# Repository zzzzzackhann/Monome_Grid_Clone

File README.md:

FOR NEXT TIME:

1. Find an LED driver than operates the same way your logic decoder works for easier wiring

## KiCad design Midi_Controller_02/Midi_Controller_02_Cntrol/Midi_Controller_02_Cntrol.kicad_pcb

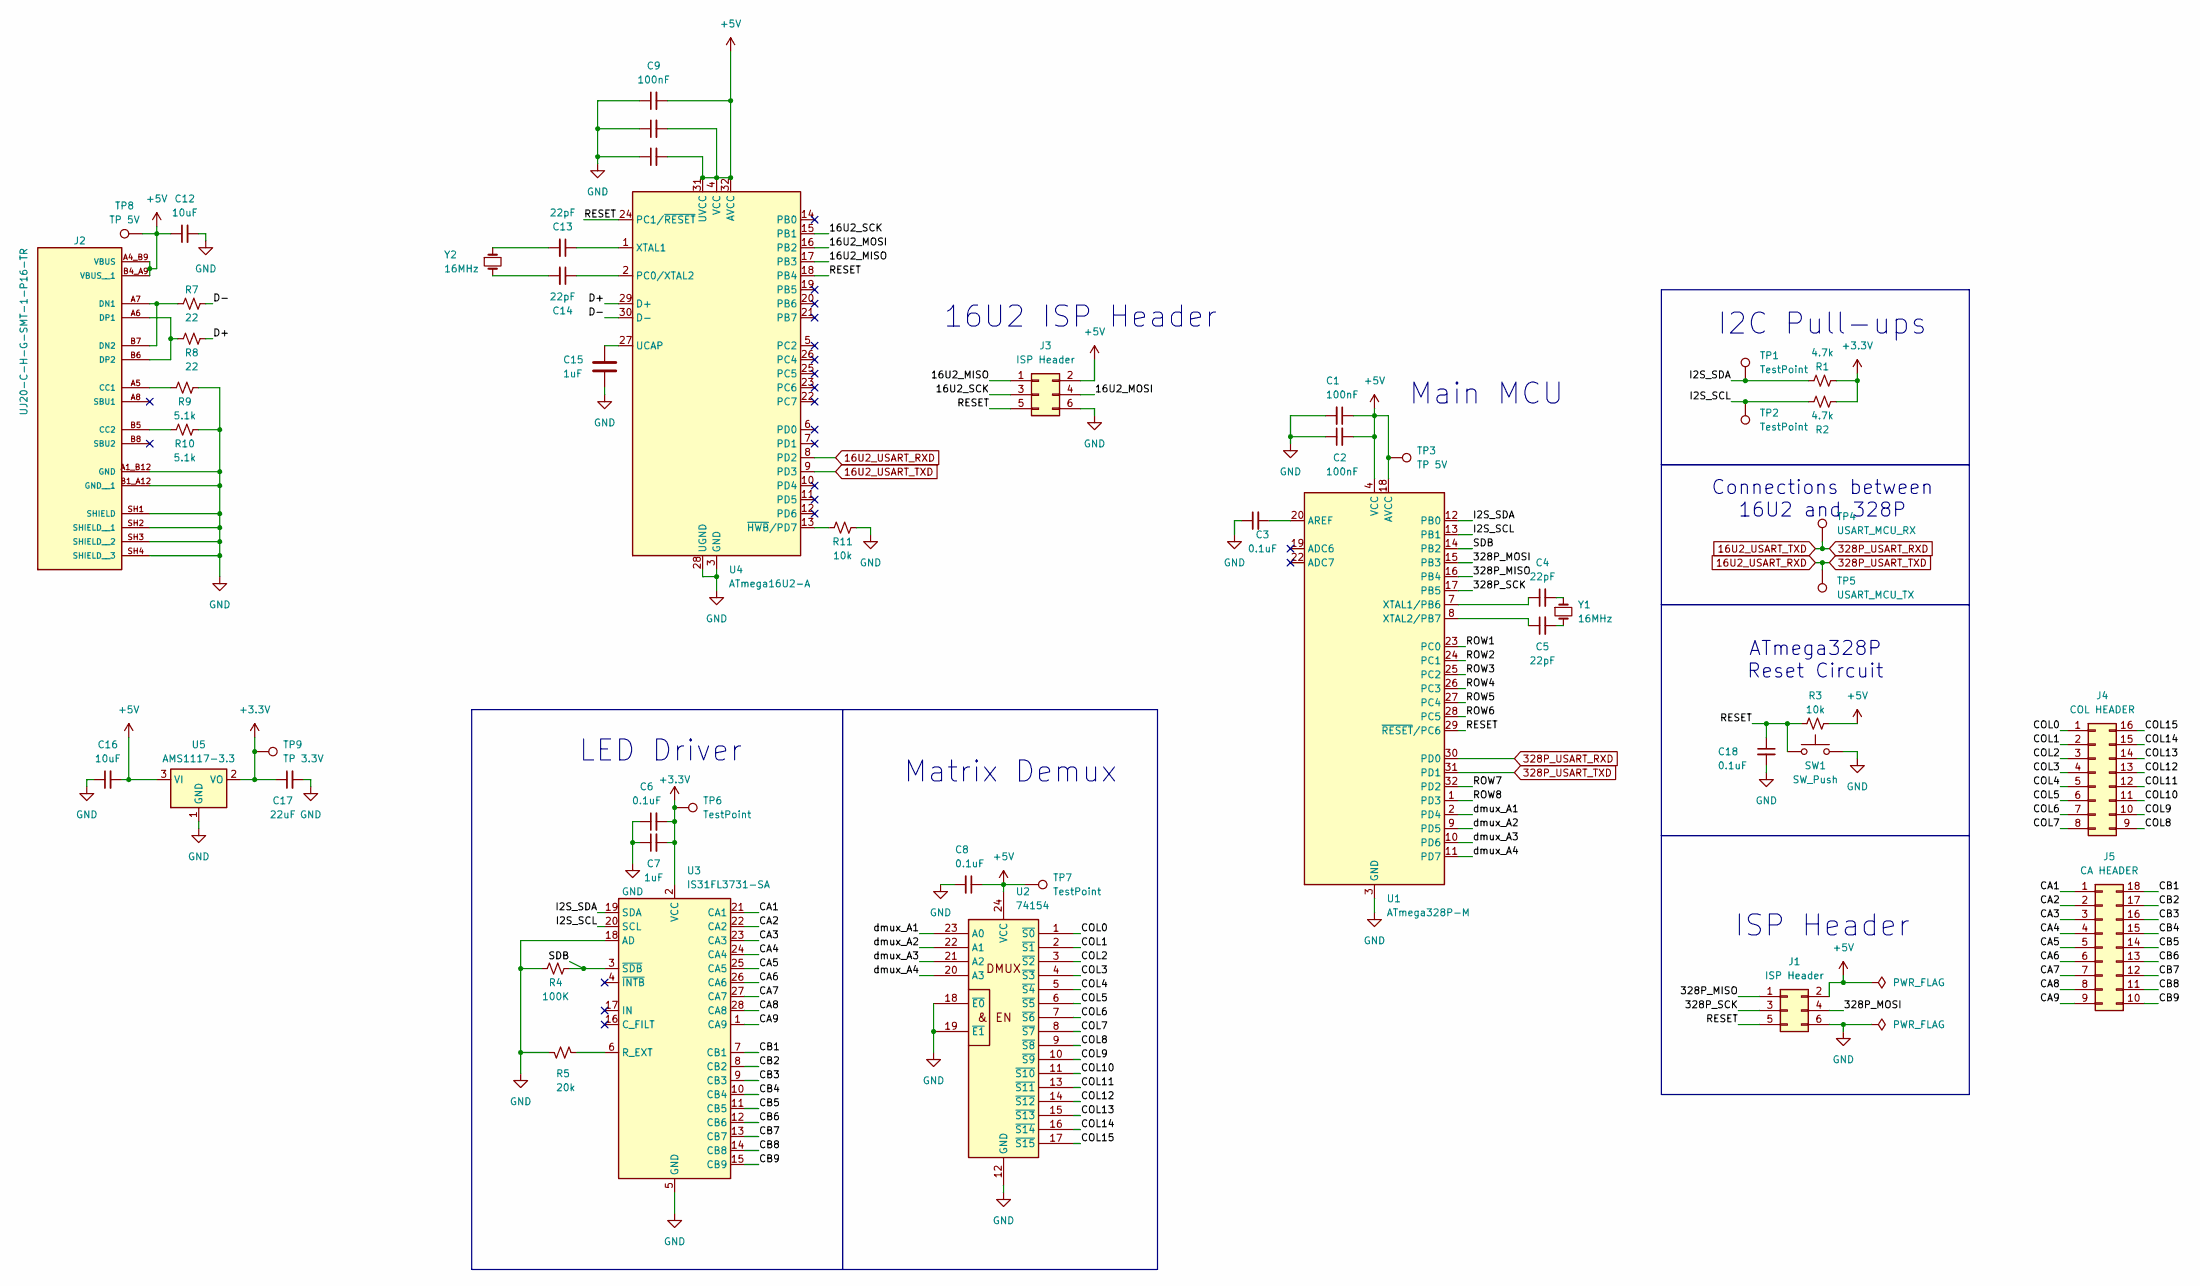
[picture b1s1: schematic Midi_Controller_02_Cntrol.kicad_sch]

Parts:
C1, C2, C9, C10, C11: 100nF; C_0805_2012Metric
C3, C6, C8, C18: 0.1uF; C_0805_2012Metric
C4, C5, C13, C14: 22pF; C_0805_2012Metric
C7, C15: 1uF; C_0805_2012Metric
C12, C16: 10uF; C_0805_2012Metric
C17: 22uF; C_0805_2012Metric
J1, J3: ISP Header; TestPoint_Pad_D1.0mm_2x3
J2: UJ20-C-H-G-SMT-1-P16-TR; SAMESKY_UJ20-C-H-G-SMT-1-P16-TR; PARTREV 1.0
J4: COL HEADER; PinHeader_2x08_P2.54mm_Horizontal
J5: CA HEADER; PinHeader_2x09_P2.54mm_Horizontal
R1, R2: 4.7k; R_0805_2012Metric
R3, R11: 10k; R_0805_2012Metric
R4: 100K; R_0805_2012Metric
R5: 20k; R_0805_2012Metric
R7, R8: 22; R_0805_2012Metric
R9, R10: 5.1k; R_0805_2012Metric
SW1: SW_Push; SW_TS04-66-55-BK-100-SMT
TP1, TP2: TestPoint; SolderWire-0.5sqmm_1x01_D0.9mm_OD2.3mm
TP3, TP8: TP 5V; TestPoint_Pad_D1.5mm
TP4: USART_MCU_RX; SolderWire-0.5sqmm_1x01_D0.9mm_OD2.3mm
TP5: USART_MCU_TX; SolderWire-0.5sqmm_1x01_D0.9mm_OD2.3mm
TP6, TP7: TestPoint; TestPoint_Pad_D1.5mm
TP9: TP 3.3V; TestPoint_Pad_D1.5mm
U1: ATmega328P-M; QFN-32-1EP_5x5mm_P0.5mm_EP3.1x3.1mm
U2: 74154; SOIC-24W_7.5x15.4mm_P1.27mm
U3: IS31FL3731-SA; SSOP-28_5.3x10.2mm_P0.65mm
U4: ATmega16U2-A; TQFP-32_7x7mm_P0.8mm
U5: AMS1117-3.3; SOT-223-3_TabPin2
Y1, Y2: 16MHz; Crystal_HC49-4H_Vertical

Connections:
16U2_USART_RXD: TP5.1 (1_1), U1.31 (PD1), U4.8 (PD2)
16U2_USART_TXD: TP4.1 (1_1), U1.30 (PD0), U4.9 (PD3)
+3.3V: C6.2, C7.2, C17.1, R1.1, R2.1, TP6.1 (1_1), TP9.1 (1_1), U3.2 (VCC), U5.2 (VO)
+5V: C1.1, C2.2, C8.1, C9.2, C10.2, C11.2, C12.1, C16.2, J1.2, J2.A4_B9 (VBUS), J2.B4_A9 (VBUS__1), J3.2, R3.2, TP3.1 (1_1), TP7.1 (1_1), TP8.1 (1_1), U1.4 (VCC), U1.6 (VCC), U1.18 (AVCC), U2.24 (VCC), U4.4 (VCC), U4.31 (UVCC), U4.32 (AVCC), U5.3 (VI)
/16U2_MISO: J3.1, U4.17 (PB3)
/16U2_MOSI: J3.4, U4.16 (PB2)
/16U2_SCK: J3.3, U4.15 (PB1)
/328P_MISO: J1.1, U1.16 (PB4)
/328P_MOSI: J1.4, U1.15 (PB3)
/328P_SCK: J1.3, U1.17 (PB5)
/CA1: J5.1, U3.21 (CA1)
/CA2: J5.2, U3.22 (CA2)
/CA3: J5.3, U3.23 (CA3)
/CA4: J5.4, U3.24 (CA4)
/CA5: J5.5, U3.25 (CA5)
/CA6: J5.6, U3.26 (CA6)
/CA7: J5.7, U3.27 (CA7)
/CA8: J5.8, U3.28 (CA8)
/CA9: J5.9, U3.1 (CA9)
/CB1: J5.18, U3.7 (CB1)
/CB2: J5.17, U3.8 (CB2)
/CB3: J5.16, U3.9 (CB3)
/CB4: J5.15, U3.10 (CB4)
/CB5: J5.14, U3.11 (CB5)
/CB6: J5.13, U3.12 (CB6)
/CB7: J5.12, U3.13 (CB7)
/CB8: J5.11, U3.14 (CB8)
/CB9: J5.10, U3.15 (CB9)
/COL0: J4.1, U2.1 (~S0)
/COL1: J4.2, U2.2 (~S1)
/COL2: J4.3, U2.3 (~S2)
/COL3: J4.4, U2.4 (~S3)
/COL4: J4.5, U2.5 (~S4)
/COL5: J4.6, U2.6 (~S5)
/COL6: J4.7, U2.7 (~S6)
/COL7: J4.8, U2.8 (~S7)
/COL8: J4.9, U2.9 (~S8)
/COL9: J4.10, U2.10 (~S9)
/COL10: J4.11, U2.11 (~S10)
/COL11: J4.12, U2.13 (~S11)
/COL12: J4.13, U2.14 (~S12)
/COL13: J4.14, U2.15 (~S13)
/COL14: J4.15, U2.16 (~S14)
/COL15: J4.16, U2.17 (~S15)
/D+: R8.1, U4.29 (D+)
/D-: R7.2, U4.30 (D-)
/I2S_SCL: R2.2, TP2.1 (1_1), U1.13 (PB1), U3.20 (SCL)
/I2S_SDA: R1.2, TP1.1 (1_1), U1.12 (PB0), U3.19 (SDA)
/RESET: C18.1, J1.5, J3.5, R3.1, SW1.1, U1.29 (~RESET/PC6), U4.18 (PB4), U4.24 (PC1/~RESET)
/ROW1: U1.23 (PC0)
/ROW2: U1.24 (PC1)
/ROW3: U1.25 (PC2)
/ROW4: U1.26 (PC3)
/ROW5: U1.27 (PC4)
/ROW6: U1.28 (PC5)
/ROW7: U1.32 (PD2)
/ROW8: U1.1 (PD3)
/SDB: R4.2, U1.14 (PB2), U3.3 (~SDB)
/dmux_A1: U1.2 (PD4), U2.23 (A0)
/dmux_A2: U1.9 (PD5), U2.22 (A1)
/dmux_A3: U1.10 (PD6), U2.21 (A2)
/dmux_A4: U1.11 (PD7), U2.20 (A3)
GND: C1.2, C2.1, C3.1, C6.1, C7.1, C8.2, C9.1, C10.1, C11.1, C12.2, C15.2, C16.1, C17.2, C18.2, J1.6, J2.A1_B12 (GND), J2.B1_A12 (GND__1), J2.SH1 (SHIELD), J2.SH2 (SHIELD__1), J2.SH3 (SHIELD__2), J2.SH4 (SHIELD__3), J3.6, R4.1, R5.1, R9.2, R10.1, R11.1, SW1.2, U1.3 (GND), U1.5 (GND), U1.21 (GND), U1.33 (GND), U2.12 (GND), U2.18 (~E0), U2.19 (~E1), U3.5 (GND), U3.18 (AD), U4.3 (GND), U4.28 (UGND), U5.1 (GND)
unnamed: C4.2, Y1.1
unnamed: C5.2, Y1.2
unnamed: C13.2, Y2.1
unnamed: C14.2, Y2.2
unnamed: J2.A5 (CC1), R9.1
unnamed: J2.B5 (CC2), R10.2
unnamed: J2.A7 (DN1), J2.B7 (DN2), R7.1
unnamed: J2.A6 (DP1), J2.B6 (DP2), R8.2
unnamed: C3.2, U1.20 (AREF)
unnamed: C4.1, U1.7 (XTAL1/PB6)
unnamed: C5.1, U1.8 (XTAL2/PB7)
unnamed: R5.2, U3.6 (R_EXT)
unnamed: C14.1, U4.2 (PC0/XTAL2)
unnamed: C15.1, U4.27 (UCAP)
unnamed: C13.1, U4.1 (XTAL1)
unnamed: R11.2, U4.13 (~HWB/PD7)

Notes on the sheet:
Main MCU
LED Driver
ISP Header
I2C Pull-ups
Connections between 16U2 and 328P
ATmega328P Reset Circuit
16U2 ISP Header
Matrix Demux

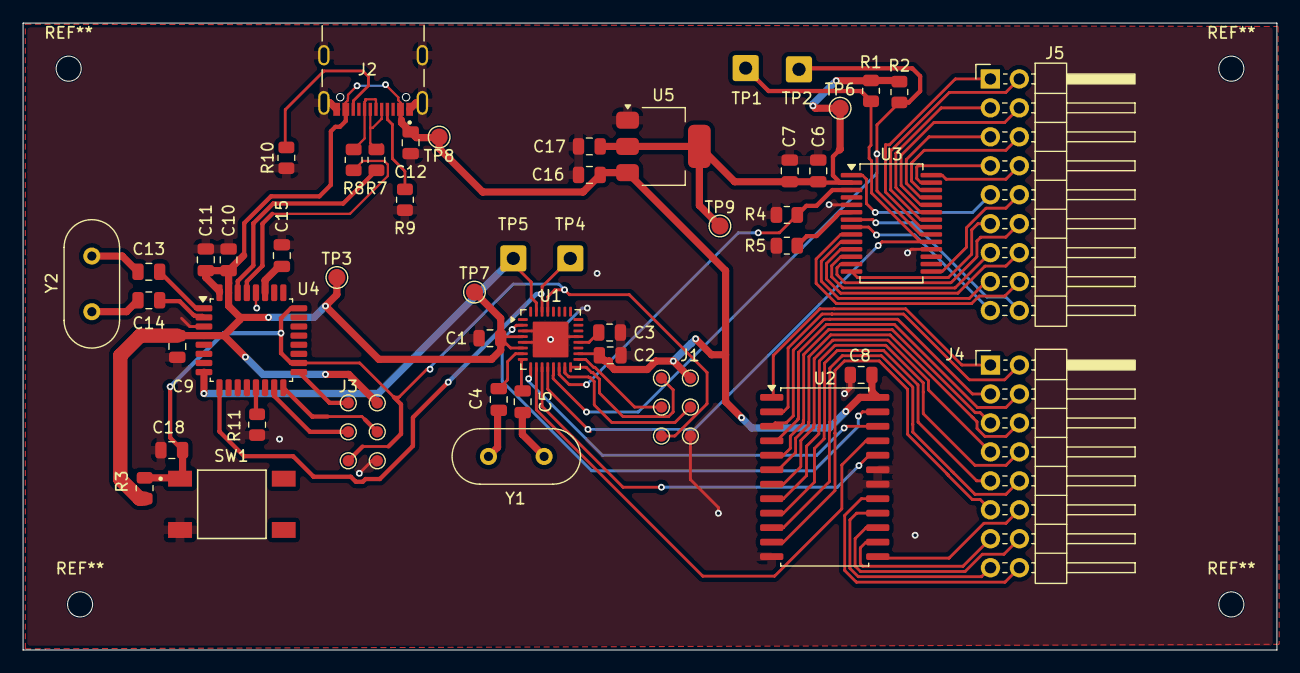
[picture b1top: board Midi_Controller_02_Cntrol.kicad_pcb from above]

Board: 2 copper layers, 110.0 x 55.0 mm, 50 parts (0 on the bottom side), 71 nets.

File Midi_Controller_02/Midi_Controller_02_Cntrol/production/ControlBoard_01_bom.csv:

Designator,Footprint,Quantity,Value,LCSC Part #
"C1, C10, C11, C2, C9",0805,5,100nF,
"C12, C16",0805,2,10uF,
"C13, C14, C4, C5",0805,4,22pF,
"C15, C7",0805,2,1uF,
C17,0805,1,20uF,
"C18, C3, C6, C8",0805,4,0.1uF,
"J1, J3",TestPoint_Pad_D1.0mm_2x3,2,ISP Header,
J2,SAMESKY_UJ20-C-H-G-SMT-1-P16-TR,1,UJ20-C-H-G-SMT-1-P16-TR,
J4,PinHeader_2x08_P2.54mm_Horizontal,1,COL HEADER,
J5,PinHeader_2x09_P2.54mm_Horizontal,1,CA HEADER,
"R1, R2",0805,2,4.7k,
"R10, R9",0805,2,5.1k,
"R11, R3",0805,2,10k,
R4,0805,1,100K,
R5,0805,1,20k,
"R7, R8",0805,2,22,
SW1,SW_TS04-66-55-BK-100-SMT,1,SW_Push,
"TP1, TP2",SolderWire-0.5sqmm_1x01_D0.9mm_OD2.3mm,2,TestPoint,
"TP3, TP8",TestPoint_Pad_D1.5mm,2,TP 5V,
TP4,SolderWire-0.5sqmm_1x01_D0.9mm_OD2.3mm,1,USART_MCU_RX,
TP5,SolderWire-0.5sqmm_1x01_D0.9mm_OD2.3mm,1,USART_MCU_TX,
"TP6, TP7",TestPoint_Pad_D1.5mm,2,TestPoint,
TP9,TestPoint_Pad_D1.5mm,1,TP 3.3V,
U1,QFN-32-1EP_5x5mm_P0.5mm_EP3.1x3.1mm,1,ATmega328P-M,
U2,SOIC-24W_7.5x15.4mm_P1.27mm,1,74154,
U3,SSOP-28_5.3x10.2mm_P0.65mm,1,IS31FL3731-SA,
U4,TQFP-32_7x7mm_P0.8mm,1,ATmega16U2-A,
U5,SOT-223-3_TabPin2,1,AMS1117-3.3,
"Y1, Y2",Crystal_HC49-4H_Vertical,2,16MHz,

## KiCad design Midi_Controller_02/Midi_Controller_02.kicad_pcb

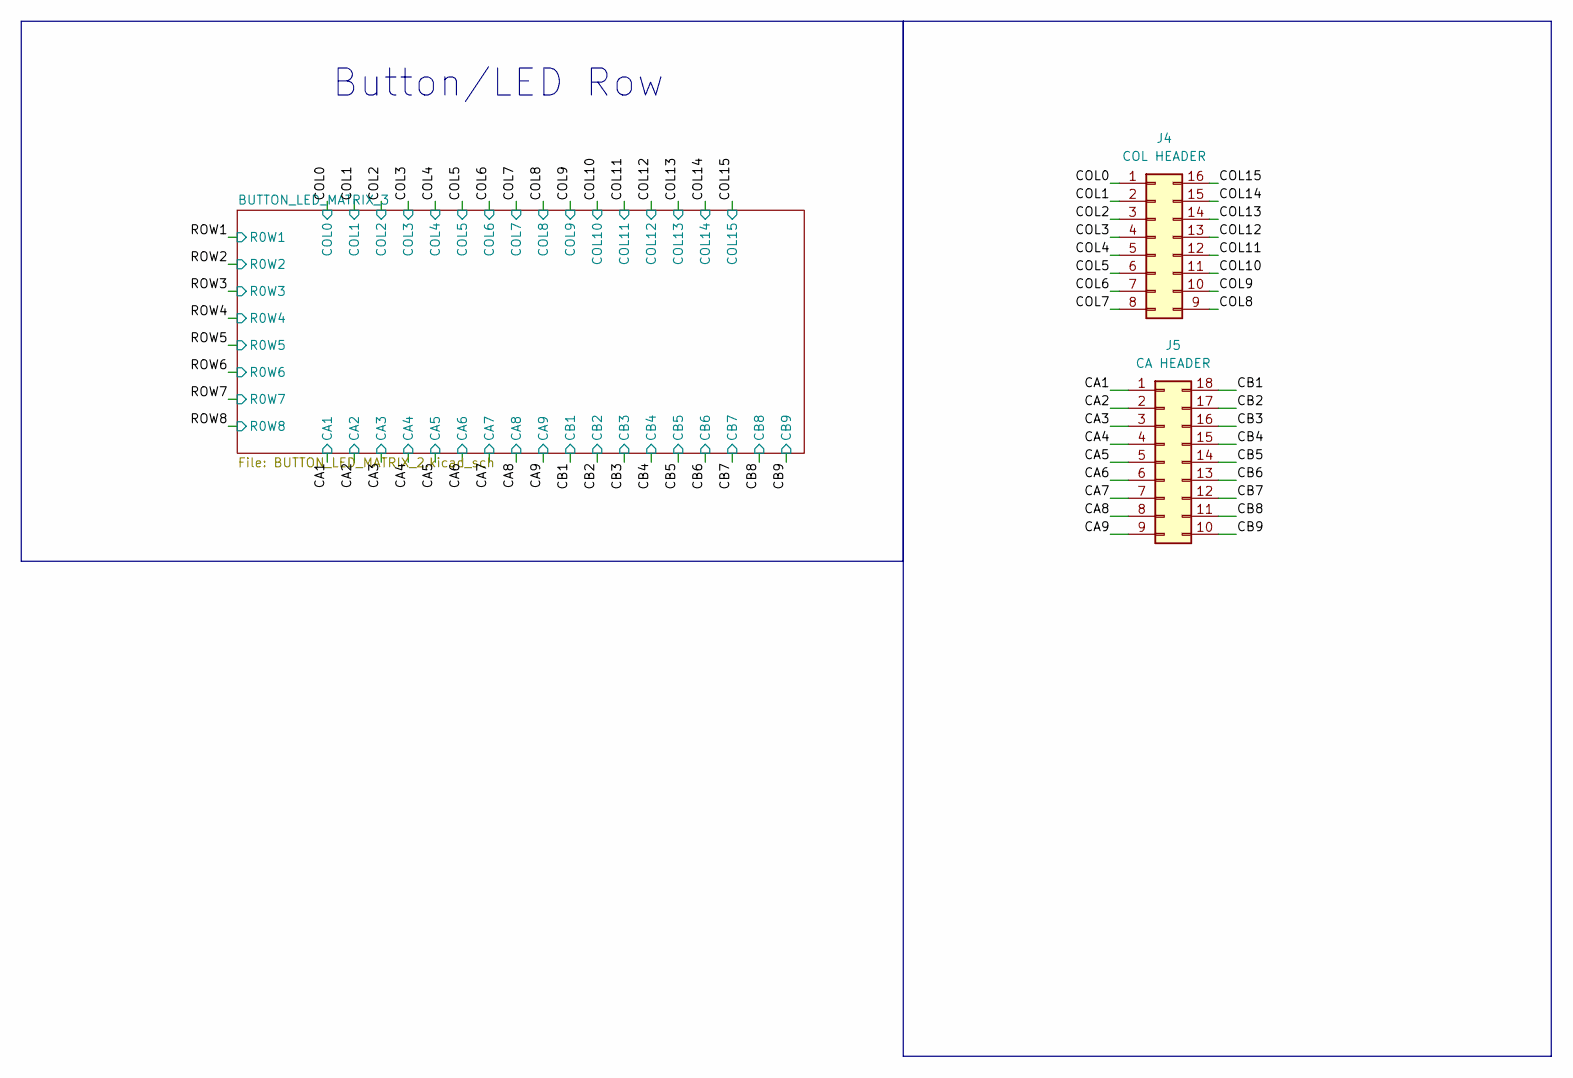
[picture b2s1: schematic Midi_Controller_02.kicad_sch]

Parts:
J4: COL HEADER; PinHeader_2x08_P2.54mm_Vertical
J5: CA HEADER; PinHeader_2x09_P2.54mm_Vertical

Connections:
/CONTROLLER-MATRIX/CA1: J5.1; also elsewhere on the board
/CONTROLLER-MATRIX/CA2: J5.2; also elsewhere on the board
/CONTROLLER-MATRIX/CA3: J5.3; also elsewhere on the board
/CONTROLLER-MATRIX/CA4: J5.4; also elsewhere on the board
/CONTROLLER-MATRIX/CA5: J5.5; also elsewhere on the board
/CONTROLLER-MATRIX/CA6: J5.6; also elsewhere on the board
/CONTROLLER-MATRIX/CA7: J5.7; also elsewhere on the board
/CONTROLLER-MATRIX/CA8: J5.8; also elsewhere on the board
/CONTROLLER-MATRIX/CA9: J5.9; also elsewhere on the board
/CONTROLLER-MATRIX/CB1: J5.18; also elsewhere on the board
/CONTROLLER-MATRIX/CB2: J5.17; also elsewhere on the board
/CONTROLLER-MATRIX/CB3: J5.16; also elsewhere on the board
/CONTROLLER-MATRIX/CB4: J5.15; also elsewhere on the board
/CONTROLLER-MATRIX/CB5: J5.14; also elsewhere on the board
/CONTROLLER-MATRIX/CB6: J5.13; also elsewhere on the board
/CONTROLLER-MATRIX/CB7: J5.12; also elsewhere on the board
/CONTROLLER-MATRIX/CB8: J5.11; also elsewhere on the board
/CONTROLLER-MATRIX/CB9: J5.10; also elsewhere on the board
/CONTROLLER-MATRIX/COL0: J4.1; also elsewhere on the board
/CONTROLLER-MATRIX/COL1: J4.2; also elsewhere on the board
/CONTROLLER-MATRIX/COL2: J4.3; also elsewhere on the board
/CONTROLLER-MATRIX/COL3: J4.4; also elsewhere on the board
/CONTROLLER-MATRIX/COL4: J4.5; also elsewhere on the board
/CONTROLLER-MATRIX/COL5: J4.6; also elsewhere on the board
/CONTROLLER-MATRIX/COL6: J4.7; also elsewhere on the board
/CONTROLLER-MATRIX/COL7: J4.8; also elsewhere on the board
/CONTROLLER-MATRIX/COL8: J4.9; also elsewhere on the board
/CONTROLLER-MATRIX/COL9: J4.10; also elsewhere on the board
/CONTROLLER-MATRIX/COL10: J4.11; also elsewhere on the board
/CONTROLLER-MATRIX/COL11: J4.12; also elsewhere on the board
/CONTROLLER-MATRIX/COL12: J4.13; also elsewhere on the board
/CONTROLLER-MATRIX/COL13: J4.14; also elsewhere on the board
/CONTROLLER-MATRIX/COL14: J4.15; also elsewhere on the board
/CONTROLLER-MATRIX/COL15: J4.16; also elsewhere on the board

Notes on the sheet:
Button/LED Row
